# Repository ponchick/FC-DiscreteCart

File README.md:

# FC-DiscreteCart

Discrete logic Famicom / Dendy cartridge PCB.

The following board types are supported:  
NROM, CNROM, GNROM, BNROM, AMROM, ANROM, AOROM, UNROM, UOROM.

Russian version: [`README.ru.md`](README.ru.md)

## Jumper configuration

All jumpers except JP1 are set according to the table below.  
JP1 (VRAM_A10) selects PPU nametable mirroring — see the note after the table.

| ROM type | U1* type | U2 type | U3 74161 | U4 7432 | U5 7402 | JP1 VRAM_A10 | JP2 PRG_OE | JP3 CHR_PIN26 | JP4 CHR_PIN27 | JP5 161_Q2 | JP6 161_Q3 | JP7 PRG_A14 | JP8 PRG_A15 | JP9 PRG_A15 | JP10 PRG_A16 | JP11 PRG_A16 | JP12 PRG_A17 |
| :--- | :--- | :--- | --- | --- | --- | --- | --- | --- | --- | --- | --- | --- | --- | --- | --- | --- | --- |
| NROM | ROM 16kB/32kB | ROM 8kB | ✗ | ✗ | ✗ | V/H\*\* |  |  |  |  |  |  |  |  |  |  |  |
| CNROM | ROM 16kB/32kB | ROM 32kB | ✓ | ✗ | ✗ | V/H\*\* |  |  |  |  |  |  |  |  |  |  |  |
| GNROM | ROM 128kB | ROM 32kB | ✓ | ✗ | ✗ | V/H\*\* |  |  |  |  |  |  |  |  |  |  |  |
| AMROM | ROM 128kB | RAM 8kB | ✓ | ✗ | ✗ |  |  |  |  |  |  |  |  |  |  |  |  |
| ANROM / AOROM | ROM 128kB/256kB | RAM 8kB | ✓ | ✗ | ✓ |  |  |  |  |  |  |  |  |  |  |  |  |
| BNROM | ROM 128kB | RAM 8kB | ✓ | ✗ | ✗ | V/H\*\* |  |  |  |  |  |  |  |  |  |  |  |
| UxROM | ROM 128kB/256kB | RAM 8kB | ✓ | ✓ | ✗ | V/H\*\* |  |  |  |  |  |  |  |  |  |  |  |

\* `U1`: for NROM/CNROM, ICs in `DIP-28` or `DIP-32` packages can be used.

\*\* JP1 (VRAM_A10) depends on the required PPU nametable mirroring:

| Mirroring | JP1 position |
| --- | --- |
| Vertical |  |
| Horizontal |  |

## License

This project is licensed under **CERN Open Hardware Licence Version 2 – Permissive** (`CERN-OHL-P-2.0`).  
See `LICENSE` for details.

SPDX-License-Identifier: `CERN-OHL-P-2.0`

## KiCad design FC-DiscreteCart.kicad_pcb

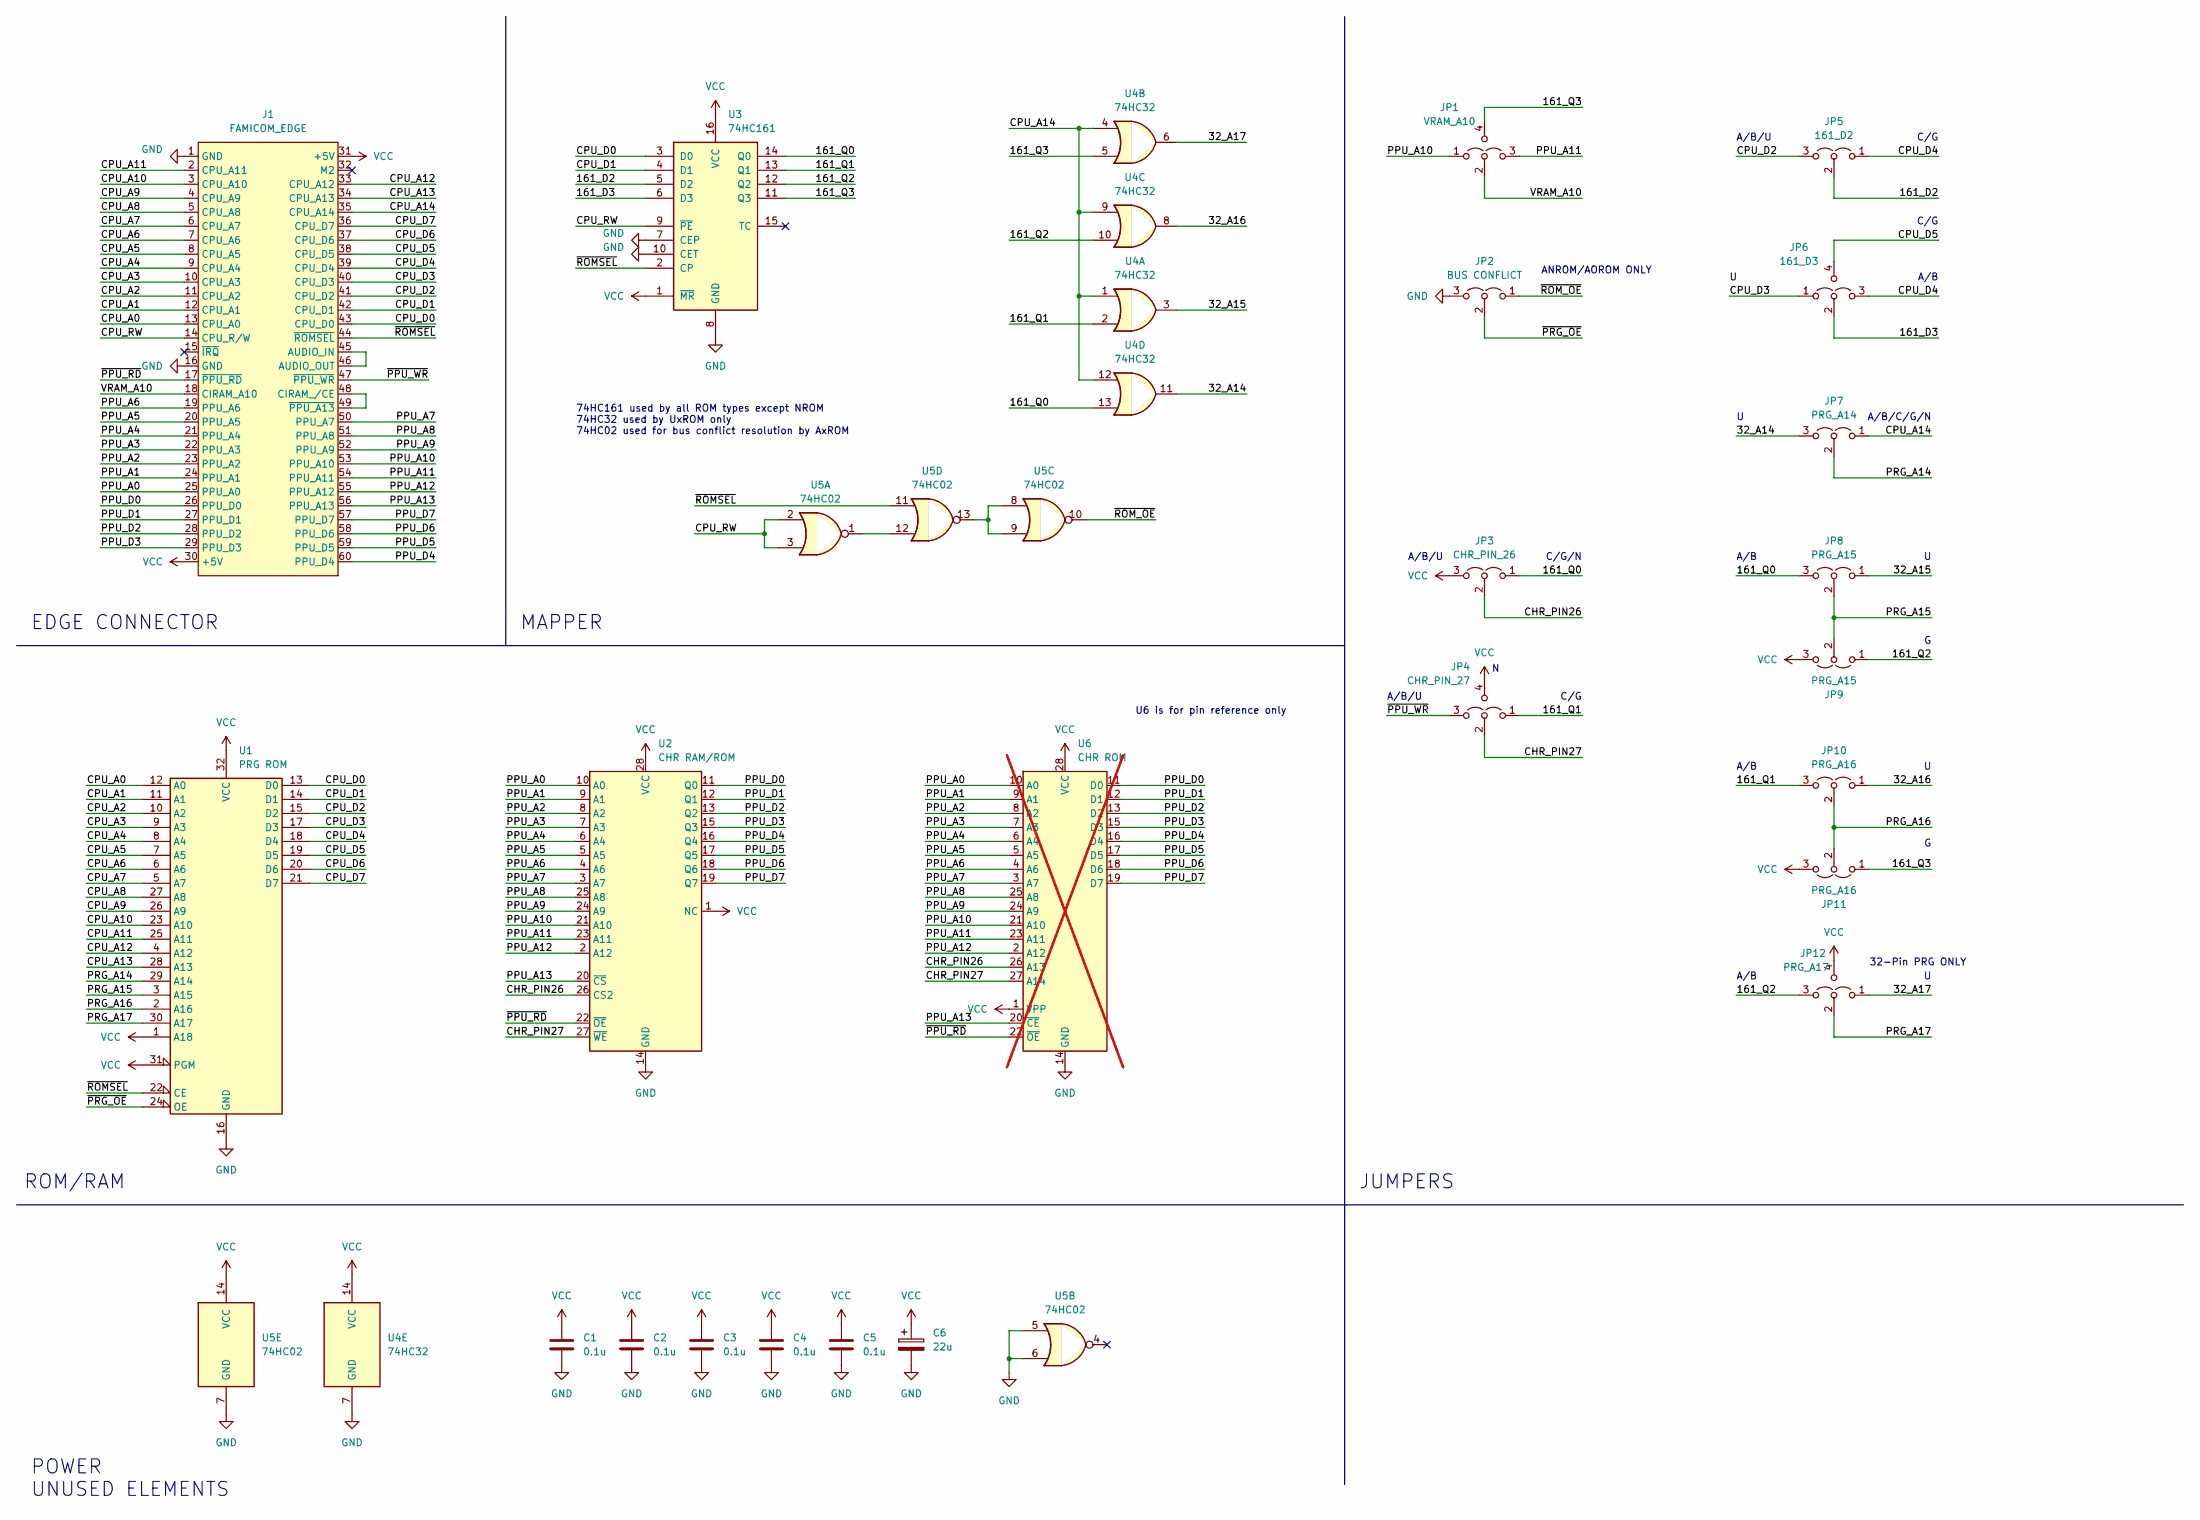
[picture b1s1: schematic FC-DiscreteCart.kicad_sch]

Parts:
C1, C2, C3, C4, C5: 0.1u; C_Disc_D4.3mm_W1.9mm_P5.00mm
C6: 22u; CP_Radial_D5.0mm_P2.50mm
J1: FAMICOM_EDGE; CONN_EDGE_2x60
JP1: VRAM_A10; SolderJumper-4
JP2: BUS CONFLICT; SolderJumper-3
JP3: CHR_PIN_26; SolderJumper-3
JP4: CHR_PIN_27; SolderJumper-4
JP5: 161_D2; SolderJumper-3
JP6: 161_D3; SolderJumper-4
JP7: PRG_A14; SolderJumper-3
JP8, JP9: PRG_A15; SolderJumper-3
JP10, JP11: PRG_A16; SolderJumper-3
JP12: PRG_A17; SolderJumper-4
U1: PRG ROM; DIP-32_W15.24mm_Socket
U2: CHR RAM/ROM; DIP-32_Triple
U3: 74HC161; DIP-16_W7.62mm
U4: 74HC32; DIP-14_W7.62mm
U5: 74HC02; DIP-14_W7.62mm
U6: CHR ROM; DIP-28_W15.24mm; not fitted

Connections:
/32_A14: JP7.3 (B), U4.11
/32_A15: JP8.1 (A), U4.3
/32_A16: JP10.1 (A), U4.8
/32_A17: JP12.1 (A), U4.6
/161_D2: JP5.2 (C), U3.5 (D2)
/161_D3: JP6.2 (C), U3.6 (D3)
/161_Q0: JP3.1 (A), JP8.3 (B), U3.14 (Q0), U4.13
/161_Q1: JP4.1 (A), JP10.3 (B), U3.13 (Q1), U4.2
/161_Q2: JP9.1 (A), JP12.3 (B), U3.12 (Q2), U4.10
/161_Q3: JP1.4 (B), JP11.1 (A), U3.11 (Q3), U4.5
/CHR_PIN26: JP3.2 (C), U2.26 (CS2), U4.26, U6.26 (A13)
/CHR_PIN27: JP4.2 (C), U2.27 (~WE), U4.27, U6.27 (A14)
/CPU_A0: J1.13 (CPU_A0), U1.12 (A0)
/CPU_A1: J1.12 (CPU_A1), U1.11 (A1)
/CPU_A2: J1.11 (CPU_A2), U1.10 (A2)
/CPU_A3: J1.10 (CPU_A3), U1.9 (A3)
/CPU_A4: J1.9 (CPU_A4), U1.8 (A4)
/CPU_A5: J1.8 (CPU_A5), U1.7 (A5)
/CPU_A6: J1.7 (CPU_A6), U1.6 (A6)
/CPU_A7: J1.6 (CPU_A7), U1.5 (A7)
/CPU_A8: J1.5 (CPU_A8), U1.27 (A8)
/CPU_A9: J1.4 (CPU_A9), U1.26 (A9)
/CPU_A10: J1.3 (CPU_A10), U1.23 (A10)
/CPU_A11: J1.2 (CPU_A11), U1.25 (A11)
/CPU_A12: J1.33 (CPU_A12), U1.4 (A12)
/CPU_A13: J1.34 (CPU_A13), U1.28 (A13)
/CPU_A14: J1.35 (CPU_A14), JP7.1 (A), U4.1, U4.4, U4.9, U4.12
/CPU_D0: J1.43 (CPU_D0), U1.13 (D0), U3.3 (D0)
/CPU_D1: J1.42 (CPU_D1), U1.14 (D1), U3.4 (D1)
/CPU_D2: J1.41 (CPU_D2), JP5.3 (B), U1.15 (D2)
/CPU_D3: J1.40 (CPU_D3), JP6.1 (A), U1.17 (D3)
/CPU_D4: J1.39 (CPU_D4), JP5.1 (A), JP6.3 (B), U1.18 (D4)
/CPU_D5: J1.38 (CPU_D5), JP6.4 (B), U1.19 (D5)
/CPU_D6: J1.37 (CPU_D6), U1.20 (D6)
/CPU_D7: J1.36 (CPU_D7), U1.21 (D7)
/CPU_RW: J1.14 (CPU_R/W), U3.9 (~PE), U5.2, U5.3
/PPU_A0: J1.25 (PPU_A0), U2.10 (A0)
/PPU_A1: J1.24 (PPU_A1), U2.9 (A1)
/PPU_A2: J1.23 (PPU_A2), U2.8 (A2)
/PPU_A3: J1.22 (PPU_A3), U2.7 (A3)
/PPU_A4: J1.21 (PPU_A4), U2.6 (A4)
/PPU_A5: J1.20 (PPU_A5), U2.5 (A5)
/PPU_A6: J1.19 (PPU_A6), U2.4 (A6)
/PPU_A7: J1.50 (PPU_A7), U2.3 (A7)
/PPU_A8: J1.51 (PPU_A8), U2.25 (A8), U4.25, U6.25 (A8)
/PPU_A9: J1.52 (PPU_A9), U2.24 (A9), U4.24, U6.24 (A9)
/PPU_A10: J1.53 (PPU_A10), JP1.1 (A), U2.21 (A10), U4.21, U6.21 (A10)
/PPU_A11: J1.54 (PPU_A11), JP1.3 (B), U2.23 (A11), U4.23, U6.23 (A11)
/PPU_A12: J1.55 (PPU_A12), U2.2 (A12)
/PPU_A13: J1.56 (PPU_A13), U2.20 (~CS), U4.20, U6.20 (~CE)
/PPU_D0: J1.26 (PPU_D0), U2.11 (Q0)
/PPU_D1: J1.27 (PPU_D1), U2.12 (Q1)
/PPU_D2: J1.28 (PPU_D2), U2.13 (Q2)
/PPU_D3: J1.29 (PPU_D3), U2.15 (Q3), U4.15, U6.15 (D3)
/PPU_D4: J1.60 (PPU_D4), U2.16 (Q4), U4.16, U6.16 (D4)
/PPU_D5: J1.59 (PPU_D5), U2.17 (Q5), U4.17, U6.17 (D5)
/PPU_D6: J1.58 (PPU_D6), U2.18 (Q6), U4.18, U6.18 (D6)
/PPU_D7: J1.57 (PPU_D7), U2.19 (Q7), U4.19, U6.19 (D7)
/PRG_A14: JP7.2 (C), U1.29 (A14)
/PRG_A15: JP8.2 (C), JP9.2 (C), U1.3 (A15)
/PRG_A16: JP10.2 (C), JP11.2 (C), U1.2 (A16)
/PRG_A17: JP12.2 (C), U1.30 (A17)
/VRAM_A10: J1.18 (CIRAM_A10), JP1.2 (C)
/~PPU_RD: J1.17 (~PPU_RD), U2.22 (~OE), U4.22, U6.22 (~OE)
/~PPU_WR: J1.47 (~PPU_WR), JP4.3 (B)
/~PRG_OE: JP2.2 (C), U1.24 (OE)
/~ROMSEL: J1.44 (~ROMSEL), U1.22 (CE), U3.2 (CP), U5.11
/~ROM_OE: JP2.1 (A), U5.10
GND: C1.2, C2.2, C3.2, C4.2, C5.2, C6.2, J1.1 (GND), J1.16 (GND), JP2.3 (B), U1.16 (GND), U2.14 (GND), U3.7 (CEP), U3.8 (GND), U3.10 (CET), U4.7 (GND), U5.5, U5.6, U5.7 (GND)
unnamed: J1.45 (AUDIO_IN), J1.46 (AUDIO_OUT)
unnamed: J1.48 (CIRAM_/CE), J1.49 (~PPU_A13)
unnamed: U5.1, U5.12
unnamed: U5.8, U5.9, U5.13
VCC: C1.1, C2.1, C3.1, C4.1, C5.1, C6.1, J1.30 (+5V), J1.31 (+5V), JP3.3 (B), JP4.4 (B), JP9.3 (B), JP11.3 (B), JP12.4 (B), U1.1 (A18), U1.31 (PGM), U1.32 (VCC), U2.1 (NC), U2.28 (VCC), U3.1 (~MR), U3.16 (VCC), U4.14 (VCC), U5.14 (VCC)

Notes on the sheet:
C/G
MAPPER
A/B/C/G/N
ANROM/AOROM ONLY
ROM/RAM
A/B
74HC161 used by all ROM types except NROM 74HC32 used by UxROM only 74HC02 used for bus conflict resolution by AxROM
A/B/U
JUMPERS
U6 is for pin reference only
32-Pin PRG ONLY
C/G/N
EDGE CONNECTOR
POWER UNUSED ELEMENTS

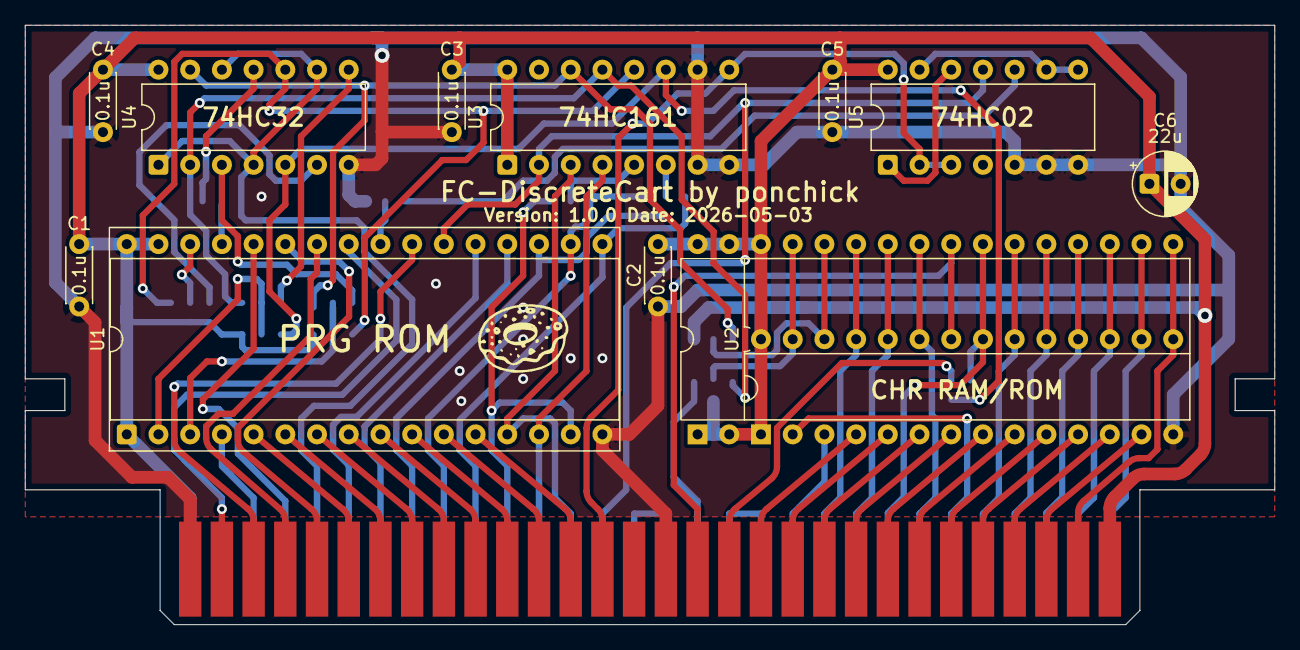
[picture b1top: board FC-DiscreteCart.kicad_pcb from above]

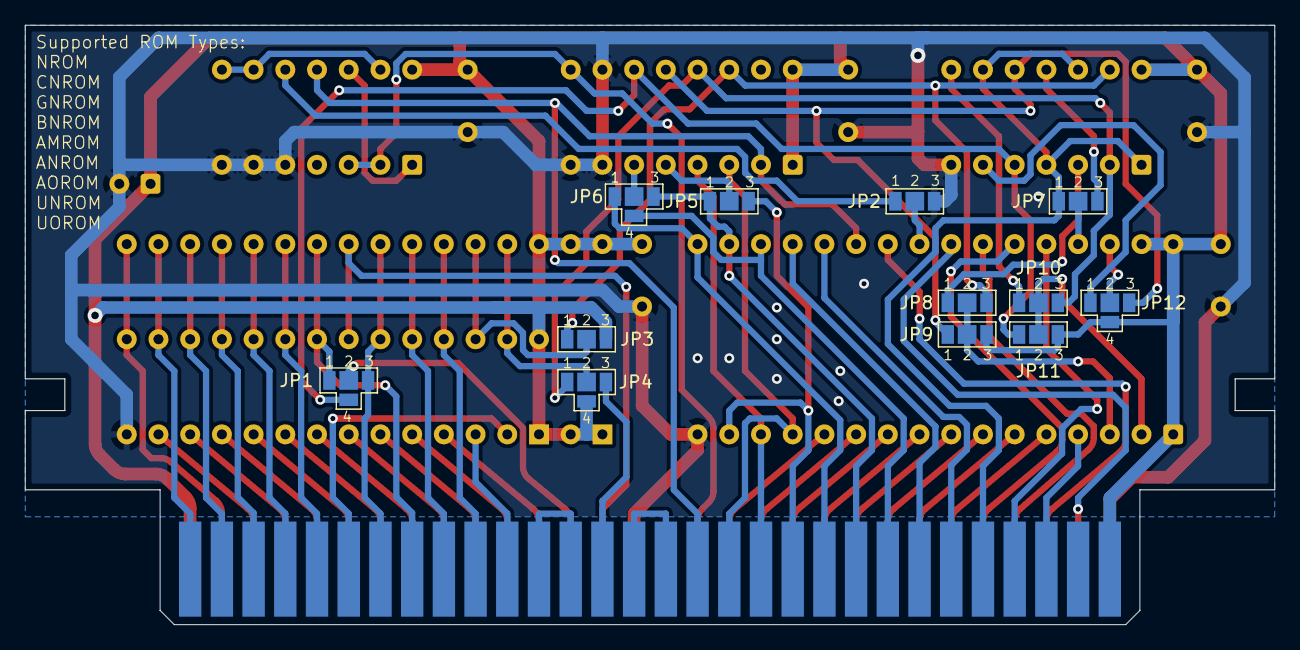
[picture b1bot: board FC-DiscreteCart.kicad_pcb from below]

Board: 2 copper layers, 100.1 x 48.0 mm, 25 parts (12 on the bottom side), 74 nets.

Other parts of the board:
LOGO#: LOGO; ponchick

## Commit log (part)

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2026-05-04 Add Jumpers.html
2026-05-06 Update README files to clarify PCB compatibility and jumper settings for Famicom/Dendy cartridges
2026-06-20 Fix image references in Jumpers.html and update README files for consistency in PCB compatibility and jumper settings.
